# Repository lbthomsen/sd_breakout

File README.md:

# SD Breakout

SD Card Breakout Board designed in KiCAD.  Production files in the pcb directory.

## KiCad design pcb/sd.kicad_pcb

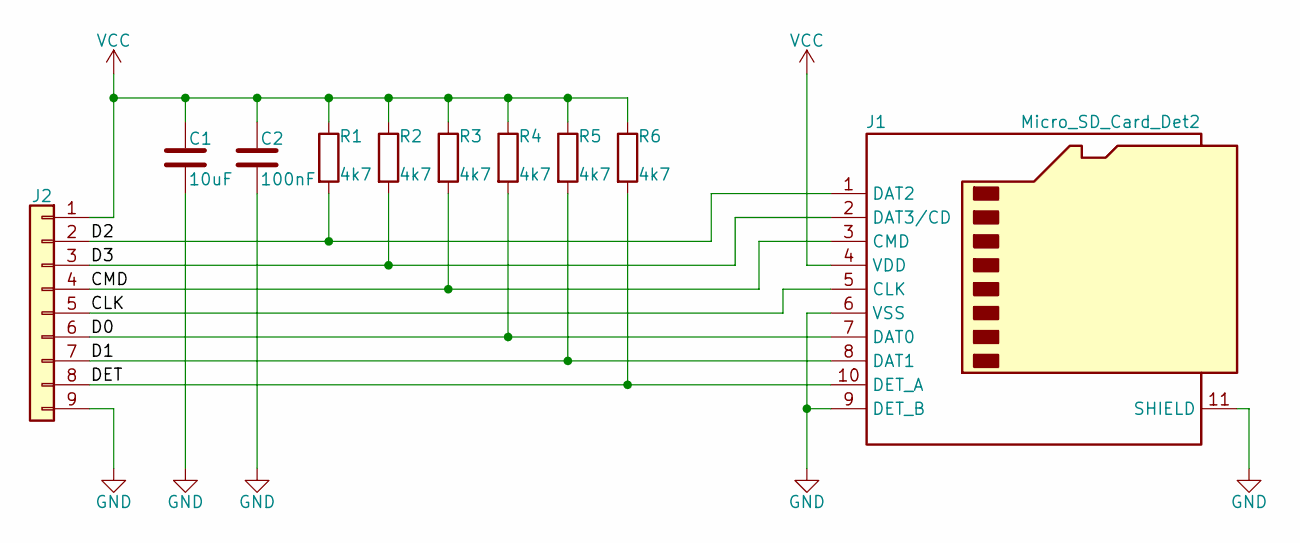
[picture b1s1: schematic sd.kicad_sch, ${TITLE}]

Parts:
C1: 10uF; C_0603_1608Metric; LCSC C19702
C2: 100nF; C_0603_1608Metric; LCSC C14663
J1: Micro_SD_Card_Det2; microSD_HC_Hirose_DM3D-SF; LCSC C719027
J2: Conn_01x09; PinHeader_1x09_P2.54mm_Vertical
R1, R2, R3, R4, R5, R6: 4k7; R_0603_1608Metric; LCSC C23162

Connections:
/CLK: J1.5 (CLK), J2.5
/CMD: J1.3 (CMD), J2.4, R3.2
/D0: J1.7 (DAT0), J2.6, R4.2
/D1: J1.8 (DAT1), J2.7, R5.2
/D2: J1.1 (DAT2), J2.2, R1.2
/D3: J1.2 (DAT3/CD), J2.3, R2.2
/DET: J1.10 (DET_A), J2.8, R6.2
GND: C1.2, C2.2, J1.6 (VSS), J1.9 (DET_B), J1.11 (SHIELD), J2.9
VCC: C1.1, C2.1, J1.4 (VDD), J2.1, R1.1, R2.1, R3.1, R4.1, R5.1, R6.1

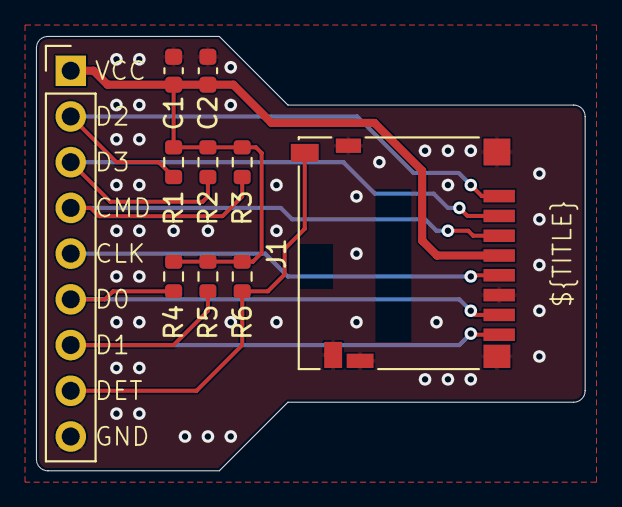
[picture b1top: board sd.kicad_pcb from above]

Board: 2 copper layers, 30.5 x 24.1 mm, 10 parts (0 on the bottom side), 9 nets.

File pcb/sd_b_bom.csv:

"Reference","Qty","Value","Footprint","Datasheet","LCSC"
"C1","1","10uF","Capacitor_SMD:C_0603_1608Metric","~","C719027"
"C2","1","100nF","Capacitor_SMD:C_0603_1608Metric","~","C14663"
"J1","1","Micro_SD_Card_Det2","Connector_Card:microSD_HC_Hirose_DM3D-SF","https://www.hirose.com/en/product/document?clcode=&productna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","C719027"
"J2","1","Conn_01x09","Connector_PinHeader_2.54mm:PinHeader_1x09_P2.54mm_Vertical","~",""
"R1,R2,R3,R4,R5,R6","6","4k7","Resistor_SMD:R_0603_1608Metric","~","C23162"

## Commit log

2025-06-01 Pretty much there
2025-06-02 Ready for order
2025-06-02 Order
2025-06-11 Bumped work revision to b. Added capacitors which may or may not be needed.
2025-06-11 More tweaks
2025-06-12 About to order
2025-06-12 Order rev_b
2025-06-12 Missed a file in commit
2025-06-14 Rev c prepared
2025-06-16 Hmmmm
2025-06-16 Hmmm
2025-06-16 Ready for order - finally - I think
